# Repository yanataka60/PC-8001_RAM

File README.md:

# PC-8001用増設32KRAMボード

　PC-8001の拡張端子に接続することで裏RAMとして使えるようになる32K増設RAMボードです。

　50Pinフラットケーブルで接続することで汎用的にも使えますが、PC-8001_SD Rev1.4に載せて使えばケーブルもいらずにコンパクトに装着できます。

　I/OポートE2hへの書込み、RAMの読み書き制御はGAL22V10が行っていますが、I/OポートE2hからの読込は対応していません。

　所有している増設RAMを必要とするゲームで試した限りではI/OポートE2hからの読込を必要としているゲームはなく、問題なく動作しました。

|名称|作者|
| ------------ | ------------ |
|AlphaDemo E2h版|きらびぃ様|
|194n|tako2様|
|New CITY HERO|内藤 時浩様|

　すべてのアプリケーション、ゲームで試したわけではないのでI/OポートE2hからの読込を必須としているものがあるかもしれませんが、I/OポートE2hからの読込対応は今のところ考えていません。

　なお、ROMDS0、ROMDS1、ROMDS2、ROMDS3信号線をまとめて制御する仕様のため、ちくらっぺさん作8kBSRAMボードとの併用はできません。

#### 2026.1.15追記 PC-8001本体との相性の悪さの原因が特定できました。一カ所のパターンカットで直ります。後述「Rev1.3基板におけるパターンカット個所」を参照してください。

## 回路図
　KiCadフォルダ内のPC-8001_RAM.pdfを参照してください。

[回路図](https://github.com/yanataka60/PC-8001_RAM/blob/main/Kicad/PC-8001_RAM.pdf)

## 部品
|番号|品名|数量|備考|
| ------------ | ------------ | ------------ | ------------ |
|J1|2x25ボックスヘッダ|1|共立エレショップ JS-1200R-50など、秋月電子通商 PH-2x40RGなどのピンヘッダでも代用可(注1)|
|J2|2x25ピンソケット|1|秋月電子通商 FH-2X25SG又はFHU-2x42SGなど|
|U1|GAL22V10|1||
||U2、U3のいずれか|||
|U2|SRAM 62256相当品|1|600mil(注2)|
|U3|SRAM CY7C199相当品|1|300mil(注2)|
|U4|74LS04|1||
|C1,C2,C4|積層セラミックコンデンサ 0.1uF|3||
|C3|電解コンデンサ 16v100uF|1||
|D1|5mm赤色LED|1|秋月電子通商 OSDR5113Aなど|
|D1|5mm緑色LED|1|秋月電子通商 OSPG5111Aなど|
|R1,R2|カーボン抵抗 330Ω|2||

　　　注1)ピンヘッダで代用するときは、基板から若干浮かせてピンヘッダをハンダ付けするとフラットケーブをスムーズに抜き差しできます。

　　　注2)U2(600mil対応)又はU3(300mil対応)のどちらか入手しやすいSRAMを使ってください。

## GALへの書込み
　Wincuplフォルダ内のRAMBORAD.jedをROMライター(TL866II Plus等)を使ってGAL22V10に書き込みます。

## 組み立ての注意点
　J2のピンソケットは基板の裏側から取り付けます。J1のボックスヘッダを取り付けるときは表側に取り付けます。

　画像ではテストのためJ1、J2の両方を取り付けていますが、どちらか接続に使用するほうだけの取付で構いません。

　SRAMは600mil、300milのどちらかを使います。画像ではテストのためU2(600mil)、U3(300mil)の両方にICソケットを取り付けていますが、使用するRAMに合わせてどちらかの取付で構いません。

　SRAM 62256相当品

.JPG)

　SRAM CY7C199相当品

## 接続
　PC-8001_SD Rev1.4に載せる場合は、PC-8001_RAMのJ2ピンソケットをPC-8001_SD Rev1.4のJ5ピンヘッダにそのままはめるだけです。

.JPG)

　フラットケーブルで接続するときはボックスヘッダの1Pinマーク(基板の「J1」と書かれたマーク)を目印にしてフラットケーブルを接続します。

## RAMのテスト
　RAMCHECKフォルダ内のramcheck.cmtを読み込み実行してください。0000h～7FFFhまでのRAMをCHECKできます。

#### 　2025.9.11 TL866ⅡPLUSで「Addr.Bus Open Circuit Test Error!」となる個体を発見できるよう改良しました。

## Rev1.3基板におけるパターンカット個所
　Rev1.3までの回路においてRAMの書込み信号線の名称を安易に「~WE」としたため、PC-8001拡張端子の「~WE」と同名となりPC-8001本体との相性を引き起こしていました。

　Rev1.3基板を修正するには画像の赤丸で囲んだ一カ所をパターンカットしてください。

## 初期3基板におけるパターンカット個所
　初期基板を修正するには基板裏面画像の赤丸で囲んだ一カ所をパターンカットしてください。

## 追記
2025.8.31 ちくらっぺさん作8kBSRAMボードとの併用は出来ないことの追記及びRAMテストプログラムの追加。

2025.9.11 TL866ⅡPLUSで「Addr.Bus Open Circuit Test Error!」となる個体を発見できるよう改良。

2025.11.11 GAL22V10とPC-8001本体との相性により動作不良が起こる場合があるので74LS04を追加。

2026.1.15 不調の原因と思われる回路の誤りを修正、基板を更新、また旧基板を修正するためのパターンカットの仕方を追加。

     謝辞:不調原因の特定にあたり、くぼちゃん様のご協力をいただきました。ありがとうございました。

2026.1.16 初期基板のパターンカット個所を追記。

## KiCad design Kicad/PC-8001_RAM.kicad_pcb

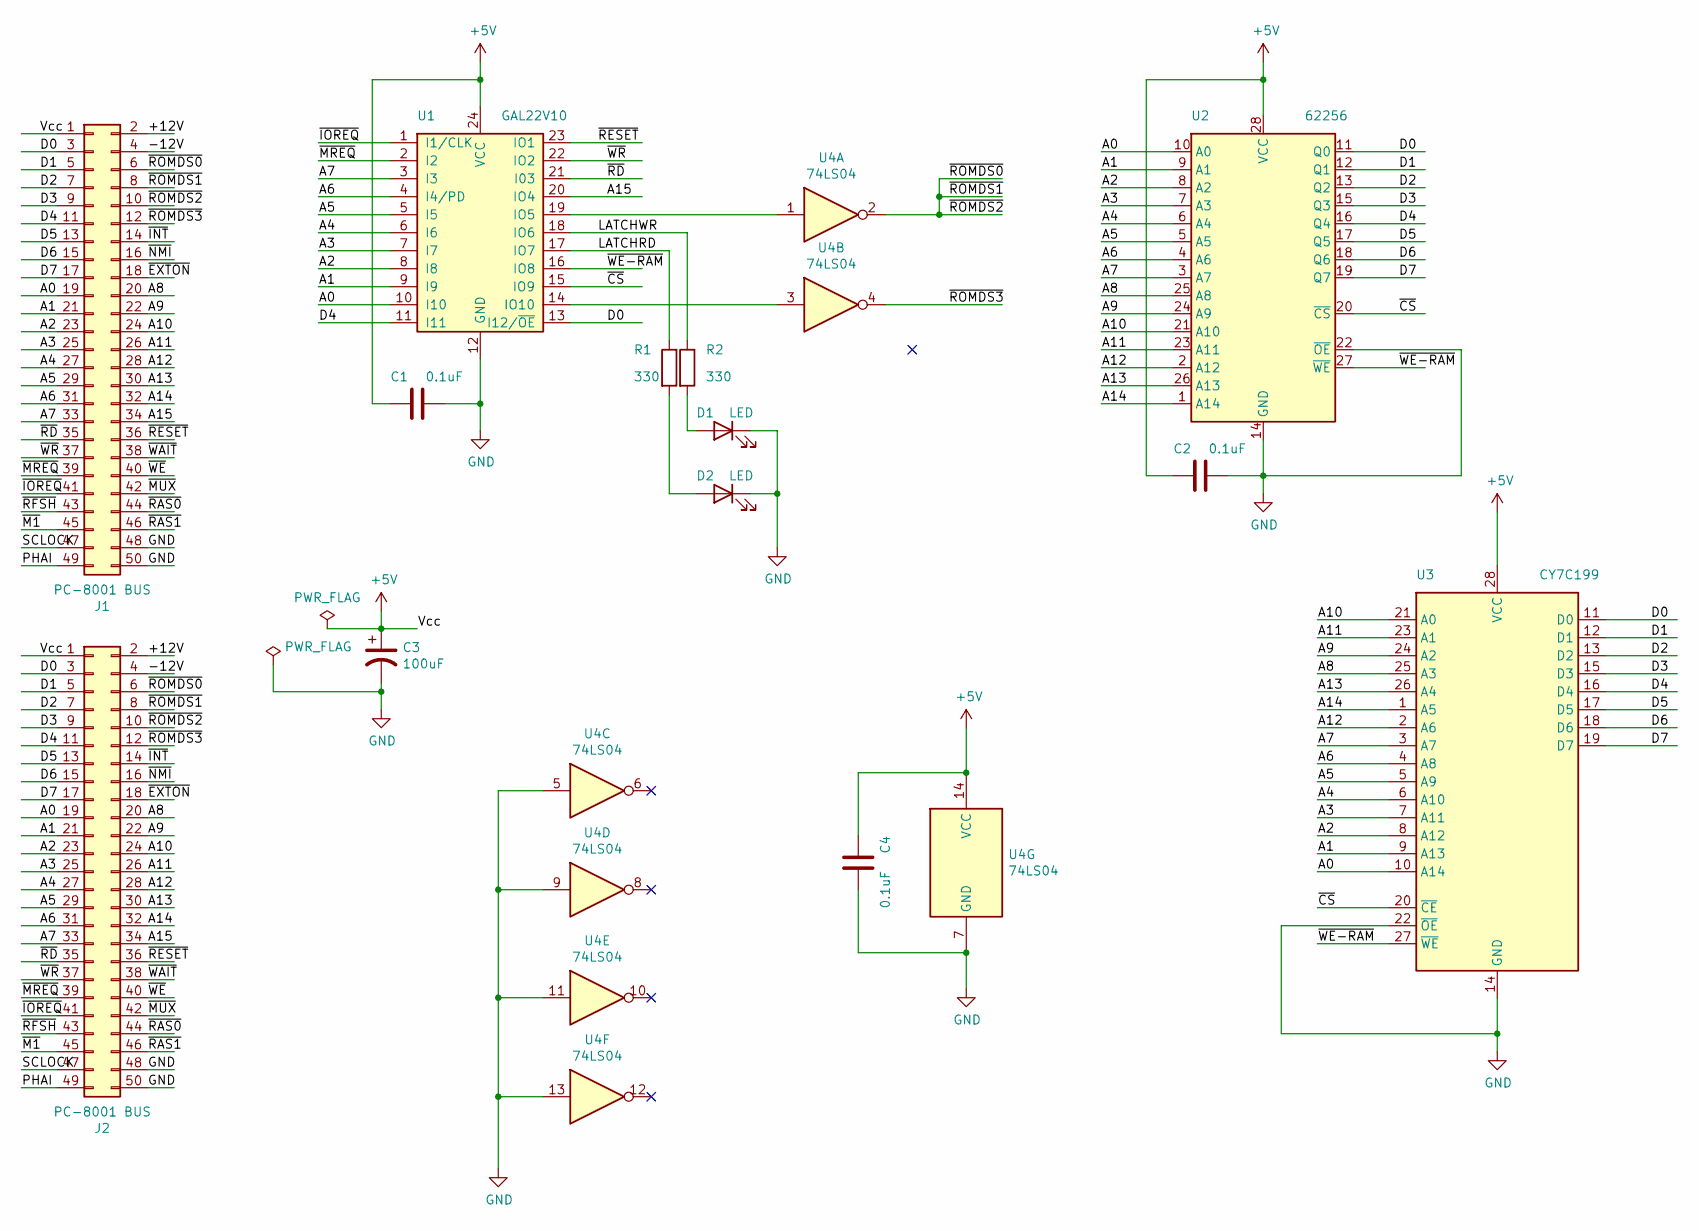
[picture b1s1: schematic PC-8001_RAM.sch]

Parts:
C1, C2, C4: 0.1uF; C_Rect_L4.0mm_W2.5mm_P2.50mm
C3: 100uF; CP_Radial_D5.0mm_P2.50mm
D1, D2: LED; LED_D5.0mm
J1: PC-8001 BUS; PinHeader_2x25_P2.54mm_Horizontal
J2: PC-8001 BUS; PinHeader_2x25_P2.54mm_Vertical
R1, R2: 330; R_Axial_DIN0207_L6.3mm_D2.5mm_P10.16mm_Horizontal
U1: GAL22V10; DIP-24_W7.62mm_LongPads
U2: 62256; DIP-28_W15.24mm_LongPads
U3: CY7C199; DIP-28_W7.62mm_LongPads
U4: 74LS04; DIP-14_W7.62mm_LongPads

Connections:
+5V: C1.1, C2.1, C3.1, C4.1, J1.1, J2.1, U1.24 (VCC), U2.28 (VCC), U3.28 (VCC), U4.14 (VCC)
/+12V: J1.2, J2.2
/-12V: J1.4, J2.4
/A0: J1.19, J2.19, U1.10 (I10), U2.10 (A0), U3.10 (A14)
/A1: J1.21, J2.21, U1.9 (I9), U2.9 (A1), U3.9 (A13)
/A2: J1.23, J2.23, U1.8 (I8), U2.8 (A2), U3.8 (A12)
/A3: J1.25, J2.25, U1.7 (I7), U2.7 (A3), U3.7 (A11)
/A4: J1.27, J2.27, U1.6 (I6), U2.6 (A4), U3.6 (A10)
/A5: J1.29, J2.29, U1.5 (I5), U2.5 (A5), U3.5 (A9)
/A6: J1.31, J2.31, U1.4 (I4/PD), U2.4 (A6), U3.4 (A8)
/A7: J1.33, J2.33, U1.3 (I3), U2.3 (A7), U3.3 (A7)
/A8: J1.20, J2.20, U2.25 (A8), U3.25 (A3)
/A9: J1.22, J2.22, U2.24 (A9), U3.24 (A2)
/A10: J1.24, J2.24, U2.21 (A10), U3.21 (A0)
/A11: J1.26, J2.26, U2.23 (A11), U3.23 (A1)
/A12: J1.28, J2.28, U2.2 (A12), U3.2 (A6)
/A13: J1.30, J2.30, U2.26 (A13), U3.26 (A4)
/A14: J1.32, J2.32, U2.1 (A14), U3.1 (A5)
/A15: J1.34, J2.34, U1.20 (IO4)
/D0: J1.3, J2.3, U1.13 (I12/~OE~), U2.11 (Q0), U3.11 (D0)
/D1: J1.5, J2.5, U2.12 (Q1), U3.12 (D1)
/D2: J1.7, J2.7, U2.13 (Q2), U3.13 (D2)
/D3: J1.9, J2.9, U2.15 (Q3), U3.15 (D3)
/D4: J1.11, J2.11, U1.11 (I11), U2.16 (Q4), U3.16 (D4)
/D5: J1.13, J2.13, U2.17 (Q5), U3.17 (D5)
/D6: J1.15, J2.15, U2.18 (Q6), U3.18 (D6)
/D7: J1.17, J2.17, U2.19 (Q7), U3.19 (D7)
/LATCHRD: R1.1, U1.17 (IO7)
/LATCHWR: R2.1, U1.18 (IO6)
/PHAI: J1.49, J2.49
/SCLOCK: J1.47, J2.47
/~CS: U1.15 (IO9), U2.20 (~CS), U3.20 (~CE~)
/~EXTON: J1.18, J2.18
/~INT: J1.14, J2.14
/~IOREQ: J1.41, J2.41, U1.1 (I1/CLK)
/~M1: J1.45, J2.45
/~MREQ: J1.39, J2.39, U1.2 (I2)
/~MUX: J1.42, J2.42
/~NMI: J1.16, J2.16
/~RAS0: J1.44, J2.44
/~RAS1: J1.46, J2.46
/~RD: J1.35, J2.35, U1.21 (I03)
/~RESET: J1.36, J2.36, U1.23 (IO1)
/~RFSH: J1.43, J2.43
/~ROMDS0: J1.6, J1.8, J1.10, J2.6, J2.8, J2.10, U4.2
/~ROMDS3: J1.12, J2.12, U4.4
/~WAIT: J1.38, J2.38
/~WE: J1.40, J2.40
/~WE-RAM: U1.16 (IO8), U2.27 (~WE), U3.27 (~WE~)
/~WR: J1.37, J2.37, U1.22 (IO2)
GND: C1.2, C2.2, C3.2, C4.2, D1.1 (K), D2.1 (K), J1.48, J1.50, J2.48, J2.50, U1.12 (GND), U2.14 (GND), U2.22 (~OE), U3.14 (GND), U3.22 (~OE~), U4.5, U4.7 (GND), U4.9, U4.11, U4.13
unnamed: D1.2 (A), R2.2
unnamed: D2.2 (A), R1.2
unnamed: U1.14 (IO10), U4.3
unnamed: U1.19 (IO5), U4.1

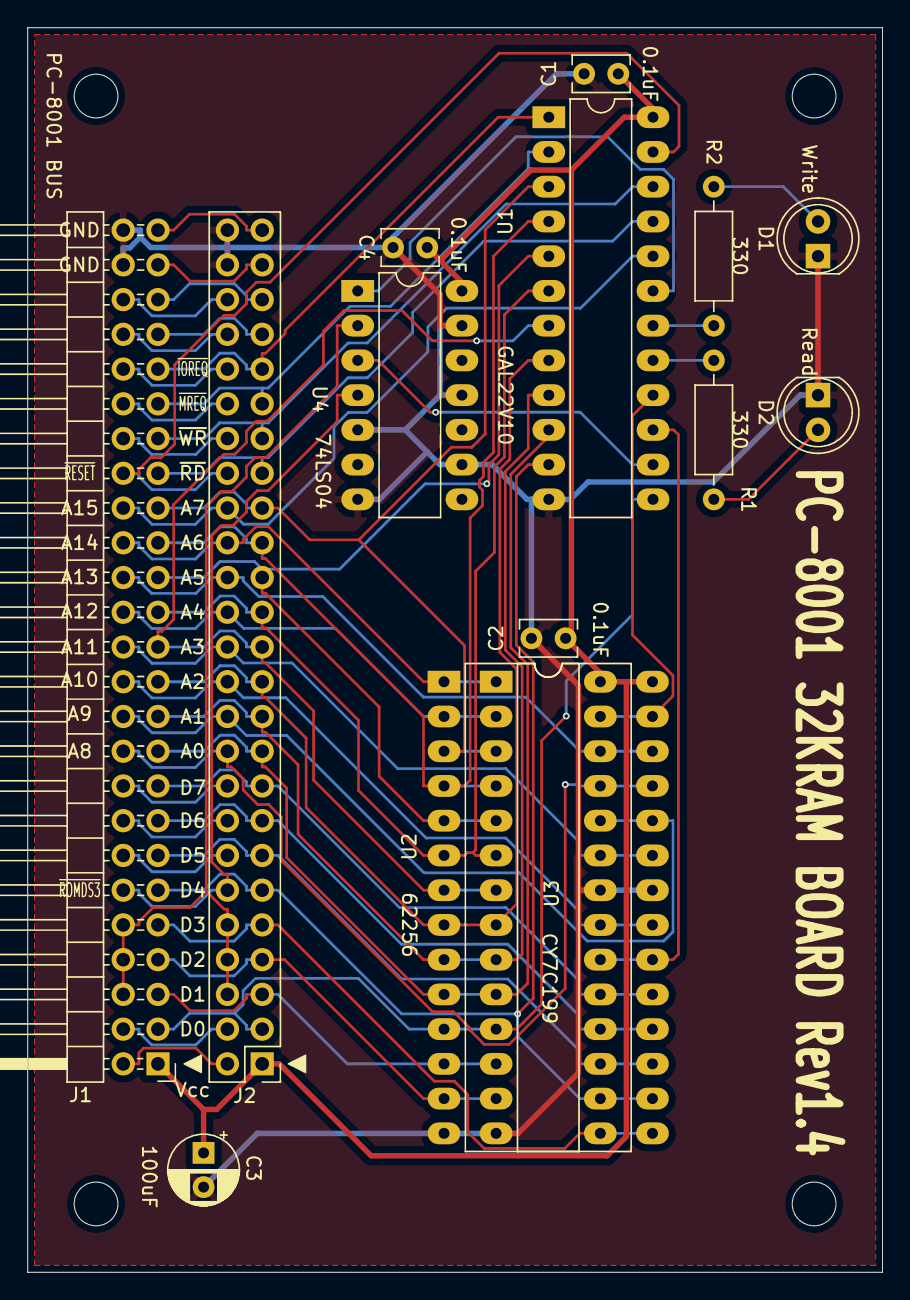
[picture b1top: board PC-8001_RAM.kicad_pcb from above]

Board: 2 copper layers, 62.5 x 91.0 mm, 18 parts (0 on the bottom side), 55 nets.

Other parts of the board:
MH1, MH2, MH3, MH4: MountingHole_3.2mm_M3
